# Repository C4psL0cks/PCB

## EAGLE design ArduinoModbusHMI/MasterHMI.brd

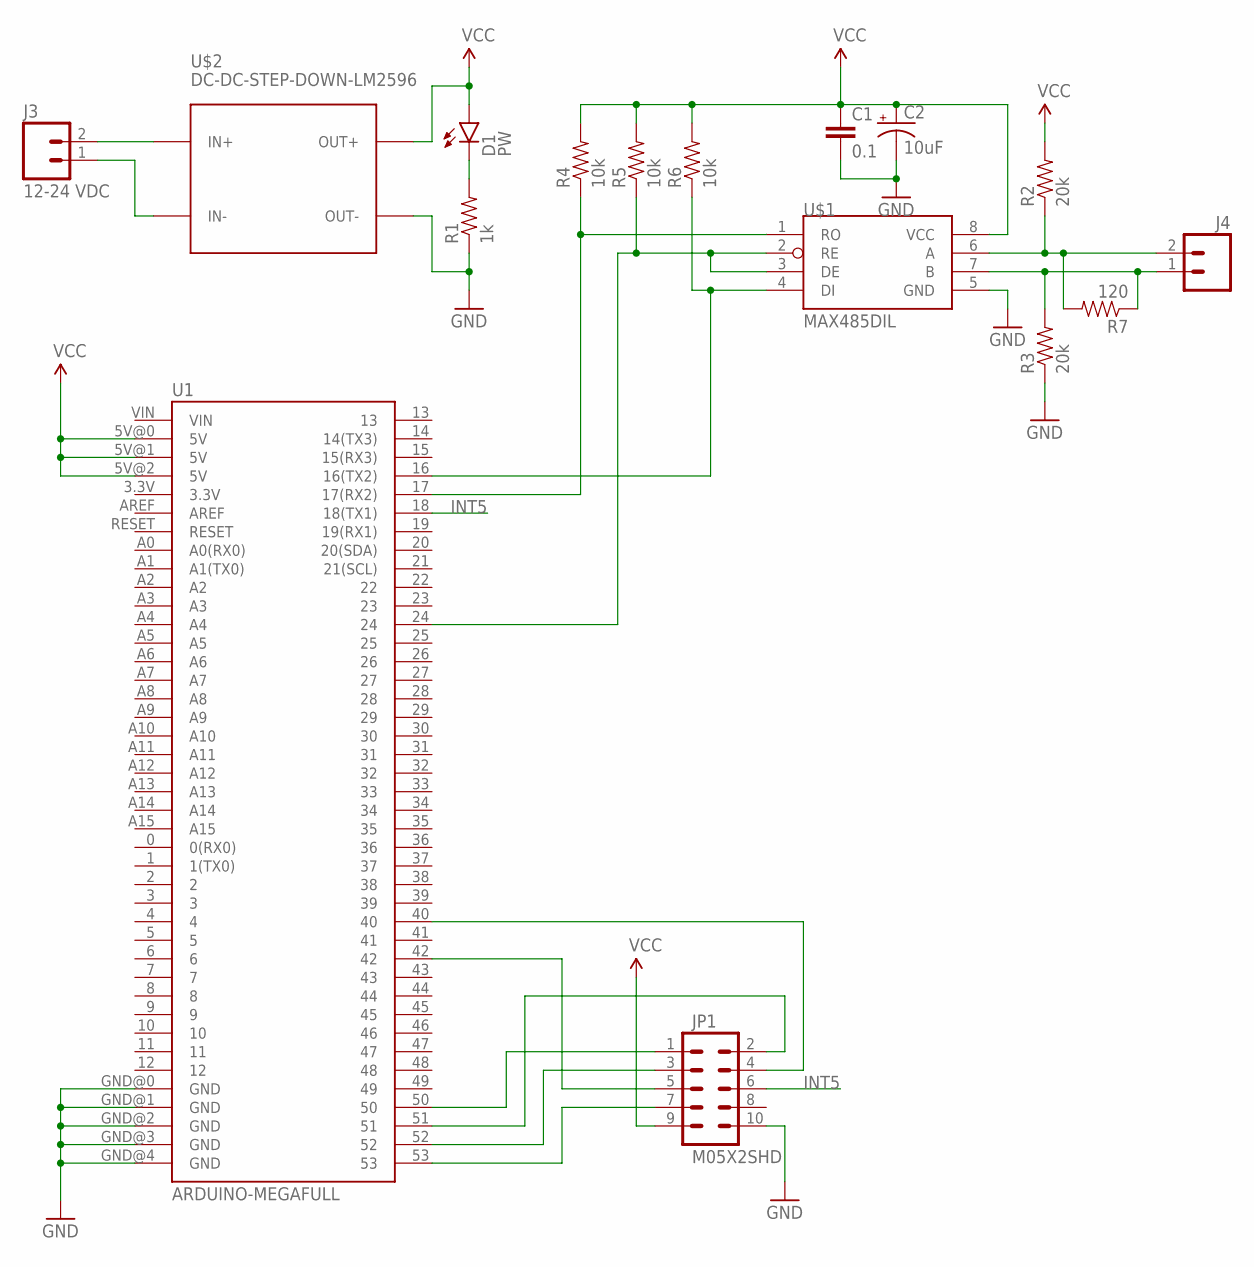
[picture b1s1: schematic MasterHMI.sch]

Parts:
C1: 0.1; CAP-PTH-5MM
C2: 10uF; CPOL-RADIAL-10UF-25V
D1: PW; LED3MM
J3: 12-24 VDC; SCREWTERMINAL-5MM-2
J4: M025MM; SCREWTERMINAL-5MM-2
JP1: M05X2SHD; 2X5-SHROUDED
R1: 1k; AXIAL-0.3
R2, R3: 20k; AXIAL-0.3
R4, R5, R6: 10k; AXIAL-0.3
R7: 120; AXIAL-0.3
U1: ARDUINO-MEGAFULL; ARDUINO_MEGA
U$1: MAX485DIL; DIL08
U$2: DC-DC-STEP-DOWN-LM2596

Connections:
GND: C1.2, C2.2 (-), JP1.10, R1.P$1 (1), R3.P$1 (1), U1.GND@0 (GND), U1.GND@1 (GND), U1.GND@2 (GND), U1.GND@3 (GND), U1.GND@4 (GND), U$1.5 (GND), U$2.OUT-
INT5: JP1.6, U1.18 (18(TX1))
unnamed: J3.2, U$2.IN+
unnamed: J3.1, U$2.IN-
unnamed: J4.2, R2.P$1 (1), R7.P$2 (2), U$1.6 (A)
unnamed: J4.1, R3.P$2 (2), R7.P$1 (1), U$1.7 (B)
unnamed: D1.K (C), R1.P$2 (2)
unnamed: JP1.1, U1.50
unnamed: JP1.2, U1.51
unnamed: R4.P$1 (1), U1.17 (17(RX2)), U$1.1 (RO)
unnamed: R6.P$1 (1), U1.16 (16(TX2)), U$1.4 (DI)
unnamed: JP1.3, U1.52
unnamed: JP1.7, U1.53
unnamed: JP1.5, U1.42
unnamed: R5.P$1 (1), U1.24, U$1.2 (RE), U$1.3 (DE)
unnamed: JP1.4, U1.40
VCC: C1.1, C2.1 (+), D1.A, JP1.9, R2.P$2 (2), R4.P$2 (2), R5.P$2 (2), R6.P$2 (2), U1.5V@0 (5V), U1.5V@1 (5V), U1.5V@2 (5V), U$1.8 (VCC), U$2.OUT+

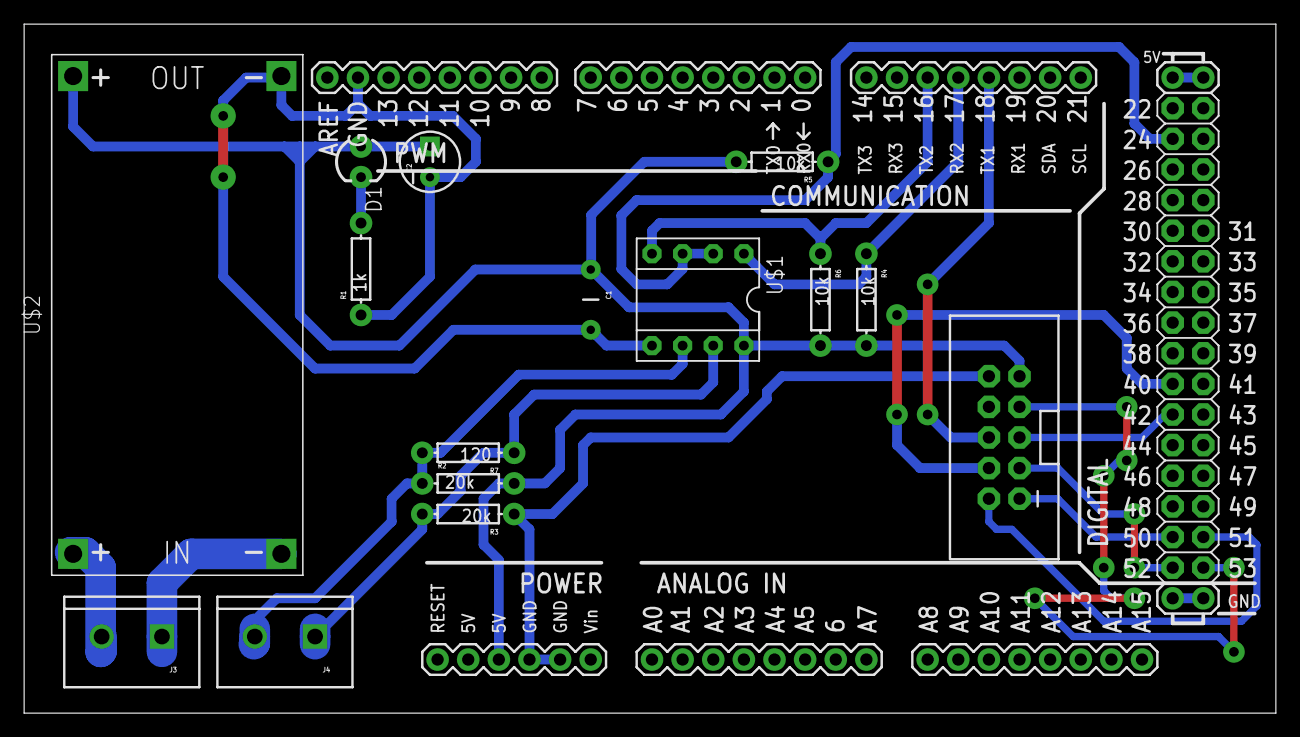
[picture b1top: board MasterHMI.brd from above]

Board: 2 copper layers, 103.8 x 57.1 mm, 16 parts (0 on the bottom side), 17 nets.

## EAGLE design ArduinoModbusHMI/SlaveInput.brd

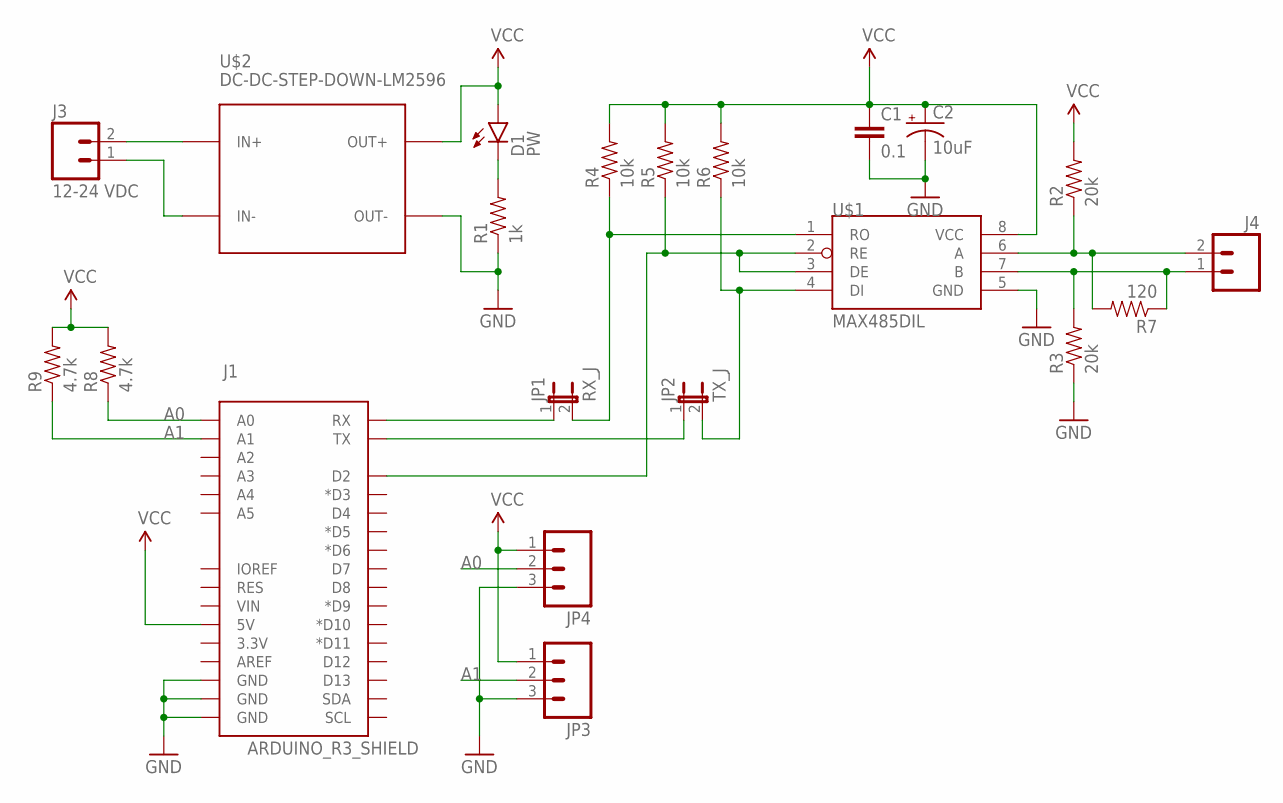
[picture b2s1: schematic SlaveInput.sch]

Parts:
C1: 0.1; CAP-PTH-5MM
C2: 10uF; CPOL-RADIAL-10UF-25V
D1: PW; LED3MM
J1: ARDUINO_R3_SHIELD; UNO_R3_SHIELD
J3: 12-24 VDC; SCREWTERMINAL-5MM-2
J4: M025MM; SCREWTERMINAL-5MM-2
JP1: RX_J; 1X02
JP2: TX_J; 1X02
JP3, JP4: M03-SCREW-5MM; SCREWTERMINAL-5MM-3
R1: 1k; AXIAL-0.3
R2, R3: 20k; AXIAL-0.3
R4, R5, R6: 10k; AXIAL-0.3
R7: 120; AXIAL-0.3
R8, R9: 4.7k; AXIAL-0.3
U$1: MAX485DIL; DIL08
U$2: DC-DC-STEP-DOWN-LM2596

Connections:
A0: J1.A0, JP4.2, R8.P$1 (1)
A1: J1.A1, JP3.2, R9.P$1 (1)
GND: C1.2, C2.2 (-), J1.GND@0 (GND), J1.GND@1 (GND), J1.GND@2 (GND), JP3.3, JP4.3, R1.P$1 (1), R3.P$1 (1), U$1.5 (GND), U$2.OUT-
unnamed: J3.2, U$2.IN+
unnamed: J3.1, U$2.IN-
unnamed: J4.2, R2.P$1 (1), R7.P$2 (2), U$1.6 (A)
unnamed: J4.1, R3.P$2 (2), R7.P$1 (1), U$1.7 (B)
unnamed: D1.K (C), R1.P$2 (2)
unnamed: J1.RX, JP1.1
unnamed: J1.TX, JP2.1
unnamed: JP1.2, R4.P$1 (1), U$1.1 (RO)
unnamed: JP2.2, R6.P$1 (1), U$1.4 (DI)
unnamed: J1.D2, R5.P$1 (1), U$1.2 (RE), U$1.3 (DE)
VCC: C1.1, C2.1 (+), D1.A, J1.5V, JP3.1, JP4.1, R2.P$2 (2), R4.P$2 (2), R5.P$2 (2), R6.P$2 (2), R8.P$2 (2), R9.P$2 (2), U$1.8 (VCC), U$2.OUT+

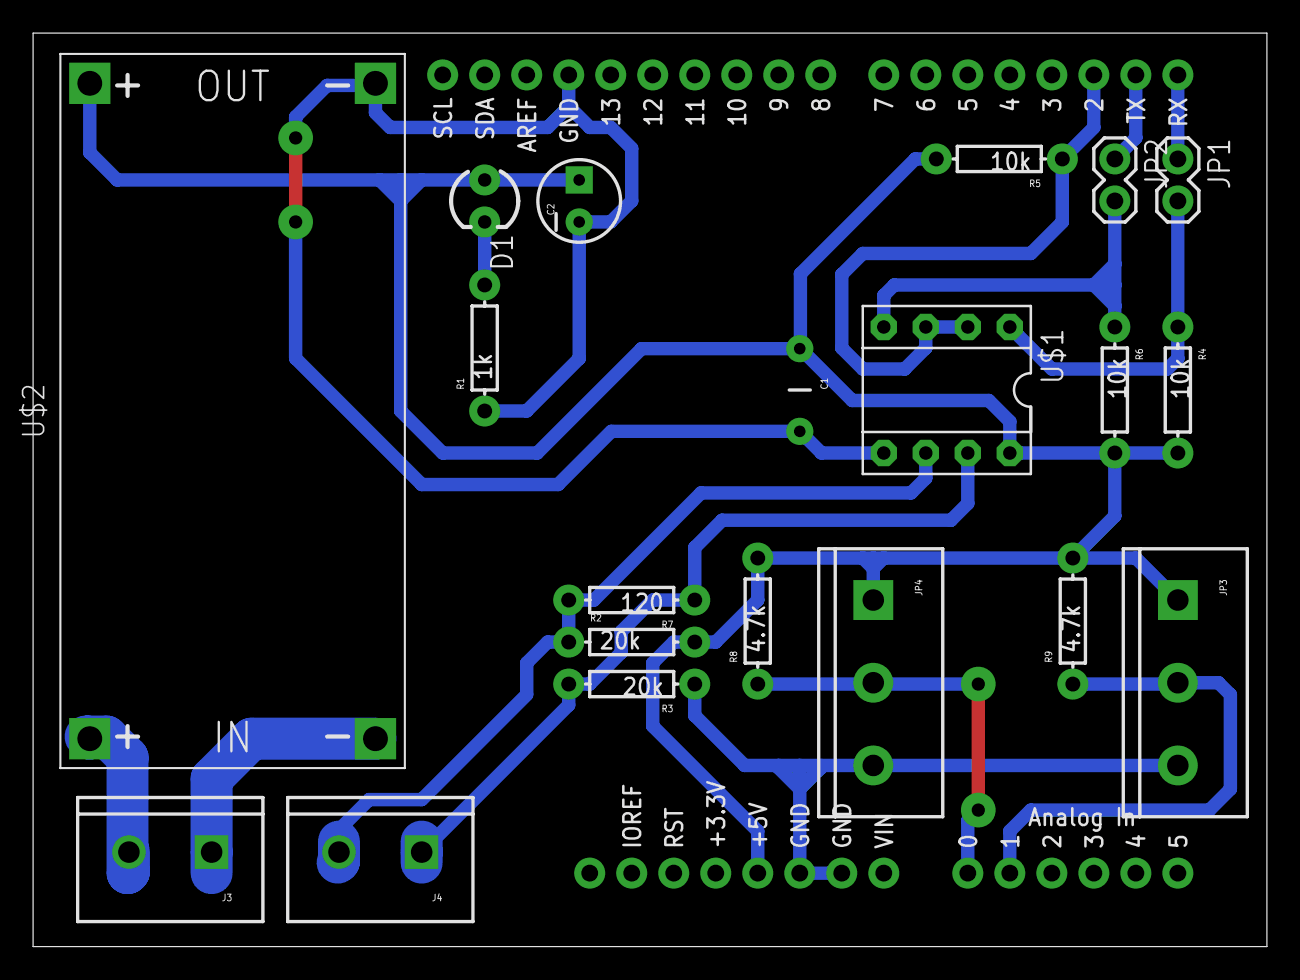
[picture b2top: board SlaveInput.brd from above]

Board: 2 copper layers, 74.6 x 55.2 mm, 21 parts (0 on the bottom side), 14 nets.

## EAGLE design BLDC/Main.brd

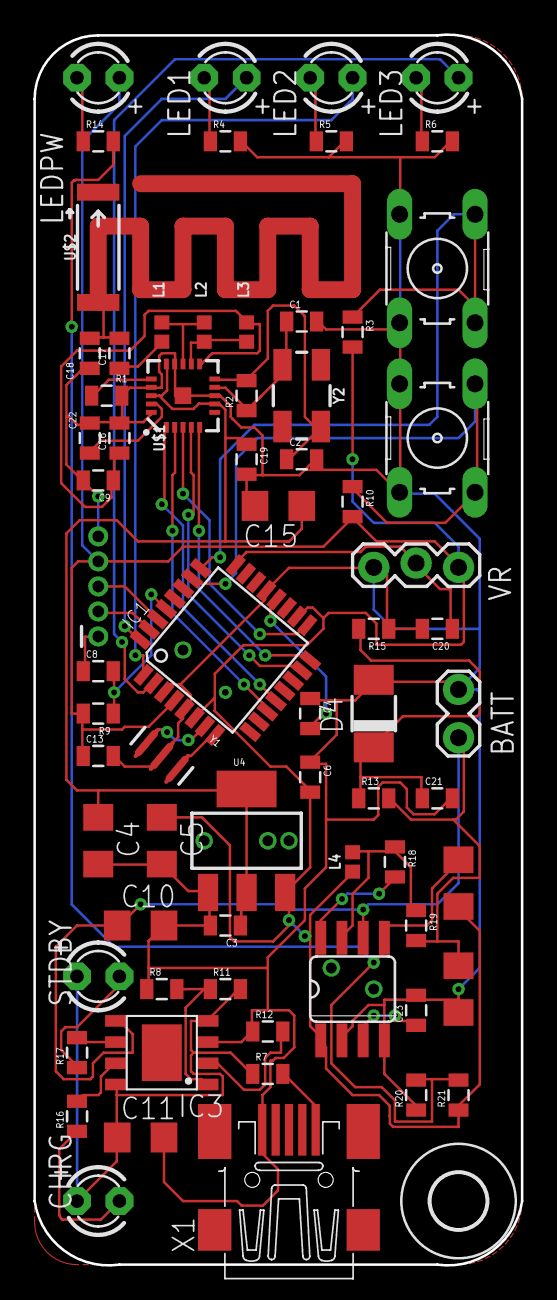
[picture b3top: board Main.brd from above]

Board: 2 copper layers, 29.2 x 73.7 mm, 70 parts (0 on the bottom side), 48 nets.

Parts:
BATT: 1X02_LOCK
C1, C2, C20: 22p; 0805
C3, C6, C7, C8, C13: 0.1uF; 0805
C4: 22uF; C1206
C5: 4.7uF; C1206
C9: 2.2nF; 0805
C10, C11, C15: 10uF; C1206
C12: 0.1mF; C1206
C14: 0.22mF; C1206
C16: 4.7p; 0805
C17: 1.5p; 0805
C18: 10p; 0805
C19: 1nF; 0805
C21: 0.1; 0805
C22: 1uF; 0805
C23: 1.5nF; 0805
CHRG: PW; LED3MM
D4: SZ105B; DO-214AC
H1: MOUNT-HOLE3.3; 3,3
IC1: MEGA8-AI; TQFP32-08
IC3: TP4056; SOP-8
J1: PIC_ICSP_MINI_5_PIN
L1: 3.9NH; 0402
L2: 8.2NH; 0402
L3: 2.7NH; 0402
L4: 100uH; 0402
LED1, LED2, LED3: PW; LED3MM
LEDPW: PW; LED3MM
R1, R14: 1k; 0805
R2: 2k; 0805
R3, R9, R10: 10k; 0805
R4, R5, R6: 330; 0805
R7, R8, R11, R12, R15: 2.2k; 0805
R13: 4.7k; 0805
R16, R17: 102; 0805
R18: 180; 0805
R19: 0.22; 0805
R20: 2.2K; 0805
R21: 6.8K; 0805
S1: SW1; B3F-10XX
S2: SW2; B3F-10XX
STDBY: PW; LED3MM
U4: LM1117 3.3; SOT223
U$1: NRF24L01SMD; QFN20-4X4MM
U$2: 2.45GHz; ANT-2.4GHZ-6.5X2.2MM
U$3: MC33063/MC34063D; SO08
VR: 1X03_LOCK
X1: MINI-USB-32005-201; 32005-201
Y1: 16MHZ; RESONATOR-SMD
Y2: CRYSTAL-SMD-5X3.2-4PAD

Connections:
3.3V: C3.1, C4.1, C15.1, C19.1, U4.2, U4.4, U$1.7, U$1.15, U$1.18
A0: C21.1, D4.C, R13.1, R15.2
A1: C20.1, IC1.24, VR.2
A2: IC1.25, R3.1, S1.3, S1.4
A3: IC1.26, R10.1, S2.3, S2.4
BATT_IN: BATT.1, C10.1, C12.1, IC3.5, R13.2, R19.2, U$3.6
D2: IC1.32, LED1.A
D3: IC1.1, LED2.A
D4: IC1.2, LED3.A
D7: IC1.11, U$1.2
D8: IC1.12, U$1.1
GND: BATT.2, C1.2, C2.2, C3.2, C4.2, C5.2, C6.1, C7.1, C9.2, C10.2, C11.2, C12.2, C13.2, C15.2, C16.2, C18.2, C19.2, C20.2, C21.2, C22.2, C23.2, D4.A, IC1.3, IC1.5, IC1.21, IC3.3, J1.5, R1.2, R4.2, R5.2, R6.2, R8.1, R12.1, R15.1, R20.1, S1.1, S1.2, S2.1, S2.2, U4.1, U$1.0, U$1.8, U$1.14, U$1.17, U$1.20, U$3.2, U$3.4, VR.3, X1.1, Y1.2
MISO: IC1.16, U$1.5
MOSI: IC1.15, U$1.4
unnamed: LED1.K, R4.1
unnamed: LED2.K, R5.1
unnamed: LED3.K, R6.1
unnamed: C17.1, L1.2
unnamed: IC1.8, Y1.3
unnamed: IC1.7, Y1.1
unnamed: C7.2, IC1.20
unnamed: C8.1, J1.1
unnamed: LEDPW.K, R14.1
unnamed: IC3.7, R16.2
unnamed: L1.1, L2.1, U$1.13
unnamed: L2.2, L3.2, U$1.12
unnamed: C9.1, C16.1, L3.1, U$1.11
unnamed: C22.1, U$1.19
unnamed: R1.1, U$1.16
unnamed: C17.2, C18.1, U$2.FEED
unnamed: C1.1, R2.1, U$1.9, Y2.1
unnamed: C2.1, R2.2, U$1.10, Y2.3
unnamed: IC3.6, R17.2
unnamed: R17.1, STDBY.K
unnamed: CHRG.K, R16.1
unnamed: C11.1, CHRG.A, IC3.4, IC3.8, R7.1, R11.2, STDBY.A
unnamed: C14.2, R14.2, R20.2, R21.2, U$3.5
unnamed: IC3.2, R12.2
unnamed: C23.1, U$3.3
unnamed: IC3.1, R8.2, R11.1
unnamed: R7.2, X1.5
unnamed: R18.2, U$3.8
unnamed: L4.2, R18.1, R19.1, U$3.7
RST: C8.2, IC1.29, R9.1
RXD: IC1.30, J1.3
SCK: IC1.17, U$1.3
TXD: IC1.31, J1.2
VCC: C5.1, C6.2, C13.1, C14.1, IC1.4, IC1.6, IC1.18, J1.4, L4.1, LEDPW.A, R3.2, R9.2, R10.2, R21.1, U4.3, U$3.1, VR.1

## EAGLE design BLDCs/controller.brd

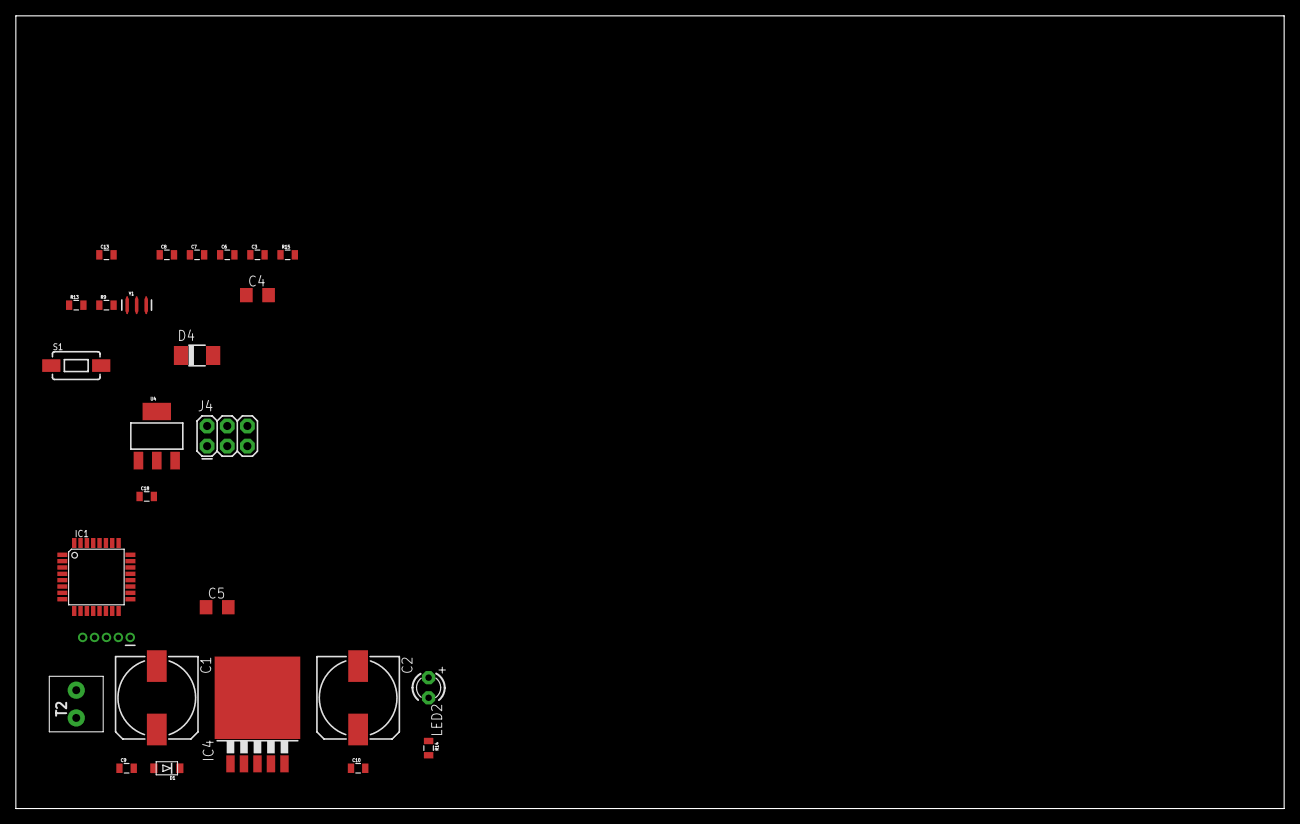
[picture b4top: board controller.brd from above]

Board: 2 copper layers, 160.0 x 100.0 mm, 27 parts (0 on the bottom side), 17 nets, no tracks yet.

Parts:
C1: 100uf; 153CLV-1010
C2: 1000uf; 153CLV-1010
C3, C6, C7, C8, C9, C10, C13: 0.1uF; 0805
C4: 22uF; C1206
C5: 4.7uF; C1206
C18: 0.1; 0805
D1: 1N5822; SOD-123FL
D4: SZ105B; DO-214AC
IC1: MEGA8-AI; TQFP32-08
IC4: LM2576HVT-5V; TO263-5
J1: PIC_ICSP_MINI_5_PIN
J4: SPI; 2X3
LED2: PW; LED3MM
R9: 10k; 0805
R13: 4.7k; 0805
R14: 1k; 0805
R15: 2.2k; 0805
S1: MCU_RST; TACTILE-SWITCH-1101NE
T2: 60VDC; ED350V-02P
U4: LM1117 3.3; SOT223
Y1: 16MHZ; RESONATOR-SMD

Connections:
3.3V: C3.1, C4.1, U4.2, U4.4
A0: C18.1, D4.C, IC1.23, R13.1, R15.2
GND: C1.-, C2.-, C3.2, C4.2, C5.2, C6.1, C7.1, C9.2, C10.2, C13.2, C18.2, D1.A, D4.A, IC1.3, IC1.5, IC1.21, IC4.3, IC4.5, J1.5, J4.6, R14.2, R15.1, S1.1, T2.P$1, U4.1, Y1.2
MISO: IC1.16, J4.1
MOSI: IC1.15, J4.4
unnamed: C1.+, C9.1, IC4.1, T2.P$2
unnamed: D1.C, IC4.2
unnamed: IC1.8, Y1.3
unnamed: IC1.7, Y1.1
unnamed: C7.2, IC1.20
unnamed: C8.1, J1.1
unnamed: LED2.K, R14.1
RST: C8.2, IC1.29, J4.5, R9.1, S1.2
RXD: IC1.30, J1.3
SCK: IC1.17, J4.3
TXD: IC1.31, J1.2
VCC: C2.+, C5.1, C6.2, C10.1, C13.1, IC1.4, IC1.6, IC1.18, IC4.4, J1.4, J4.2, LED2.A, R9.2, U4.3

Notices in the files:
parts and their libraries:
SparkFun-Capacitors: Licensing: Creative Commons ShareAlike 4.0 International - https://creativecommons.org/licenses/by-sa/4.0
SparkFun: Licensing: CC v3.0 Share-Alike You are welcome to use this library for commercial purposes.
